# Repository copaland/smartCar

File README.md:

# smartCar
Arduino Bluetooth controlled 2WD smart Car

1. Ultrasonic sensor
2. Bluetooth controlled with Button App
3. Bluetooth controlled with Joystic App  

[AF Motor Shield Library] https://github.com/adafruit/Adafruit-Motor-Shield-library

https://arduino.esp8266.com/stable/package_esp8266com_index.json

https://github.com/stm32duino/BoardManagerFiles/raw/master/package_stmicroelectronics_index.json,https://mcudude.github.io/MiniCore/package_MCUdude_MiniCore_index.json,https://arduino.esp8266.com/stable/package_esp8266com_index.json

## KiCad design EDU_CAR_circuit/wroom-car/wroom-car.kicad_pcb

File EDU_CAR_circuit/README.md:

## ESP-WROOM-02 BASE Smat Car Kit

### 1.KiCad 설치 : 회로도 작성, PCB 설계
### 2.Arduino 설치 : Firmware 프로그래밍
### 3.MIT APP Inventor

### ESP-WROOM-02 PIN MAP
1-A0     SENS  
2-D1   5 TRIG  
3-D2   4 ECHO  
4-D3   0 LEFT SENS(FLASH)   
5-D4   2 RIGHT SENS(SDA)  
6-D5  14 AIN(SCL)  
7-D6  12 APWM   
8-D7  13 BPWM   
9-D8  15 BIN    
10-D9  3 RX  BT  
11-D10 1 TX  BT
13-D0 16 LED (Default)  

### Use KiCad virsion 5.1.10

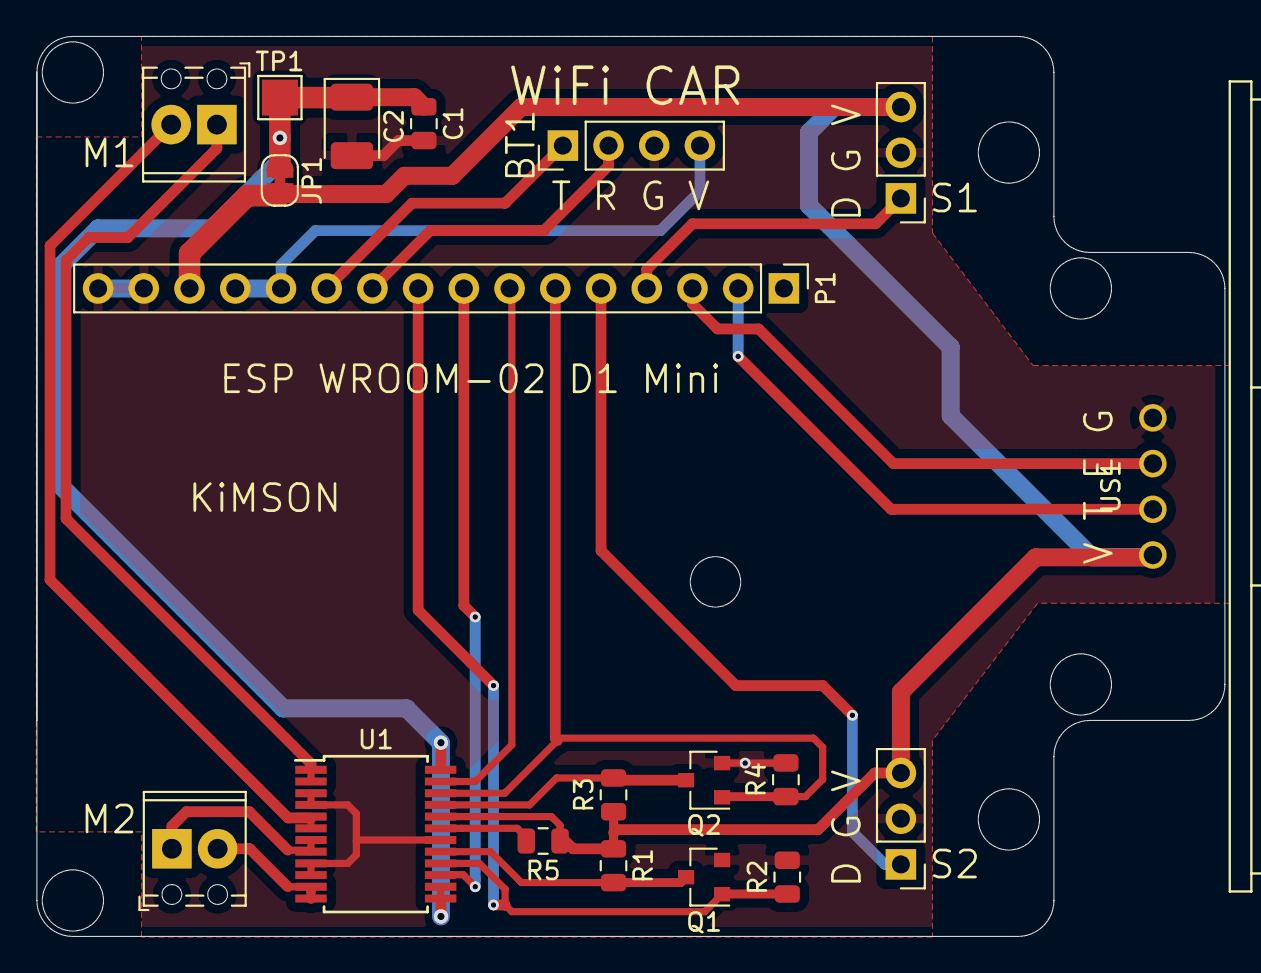
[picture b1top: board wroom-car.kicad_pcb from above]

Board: 2 copper layers, 66.0 x 50.0 mm, 19 parts (0 on the bottom side), 21 nets.

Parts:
BT1: HC-06; PinHeader_1x04_P2.54mm_Vertical
C1: 100nF; C_0805_2012Metric
C2: 22uF; CP_EIA-3528-12_Kemet-T_Pad1.50x2.35mm_HandSolder
JP1: JP; SolderJumper-2_P1.3mm_Bridged_RoundedPad1.0x1.5mm
M1, M2: Screw_Terminal_01x02; TerminalBlock_Phoenix_MPT-0,5-2-2.54_1x02_P2.54mm_Horizontal
P1: Conn_01x16_Male; PinHeader_1x16_P2.54mm_Vertical
Q1, Q2: 2N7002; SOT-23
R1, R2, R3, R4, R5: 10K; R_0805_2012Metric
S1, S2: Conn_01x03_Male; PinHeader_1x03_P2.54mm_Vertical
TP1: TestPoint; TestPoint_Pad_2.0x2.0mm
U1: TB6612FNG; SSOP-24_5.3x8.2mm_P0.65mm
US1: HC-SR04

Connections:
3V3: BT1.4, P1.12, P1.13
+5V: JP1.2, P1.14, R1.1, R3.1, R5.1, S1.3, S2.3, U1.20, US1.1
AIN: P1.6, Q2.1, R4.1, U1.22
APWM: P1.7, U1.23
BIN: P1.9, Q1.1, R2.1, U1.16
BPWM: P1.8, U1.15
ECHO: P1.3, US1.3
GND: BT1.3, C1.2, C2.2, P1.15, P1.16, Q1.2, Q2.2, R2.2, R4.2, S1.2, S2.2, U1.3, U1.4, U1.9, U1.10, U1.18, US1.4
LEFT: P1.4, S1.1
unnamed: M1.1, U1.1, U1.2
unnamed: M1.2, U1.5, U1.6
unnamed: M2.1, U1.7, U1.8
unnamed: M2.2, U1.11, U1.12
unnamed: Q1.3, R1.2, U1.17
unnamed: Q2.3, R3.2, U1.21
unnamed: R5.2, U1.19
RIGHT: P1.5, S2.1
RXD: BT1.2, P1.10
TRIG: P1.2, US1.2
TXD: BT1.1, P1.11
VS: C1.1, C2.1, JP1.1, TP1.1, U1.13, U1.14, U1.24

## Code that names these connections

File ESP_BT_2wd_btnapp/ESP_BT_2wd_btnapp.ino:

/*  20211030 ok
 *  2WD 블루투스 버튼 제어 주행 프로그램 
 *  ESP-WROOM-02 D1
D0  16 LED PULLUP 10K
D1  5 TRIG
D2  4 ECHO
D3  0      FLASH
D4  2      (SDA)
D5  14 AIN (SCL)
D6  12 APWM
D7  13 BPWM
D8  15 BIN PULLDOWN 10K 
D9  TX 1 RXD BT
D10 RX 3 TXD BT
*/
#include <ESP8266WiFi.h>
#include <WiFiCar_TB6612.h> //TB6612
#include <SoftwareSerial.h>

// pin settings
#define LED_PIN    16  //D0 
#define TRIG_PIN    5   //D1 ULTRASONIC
#define ECHO_PIN    4   //D2 

//#define OC1_PIN    0   //D3 NOT USE
//#define OC2_PIN    2   //D4 NOT USE

#define AIN_PIN    14   //D5 TB6612
#define APWM_PIN   12   //D6 
#define BPWM_PIN   13   //D7 
#define BIN_PIN    15   //D8 

#define RXD_PIN   3   //D9 BLUETOOTH TX 
#define TXD_PIN   1   //D10 BLUETOOTH RX

const int ADIR = 1; //Value can be 1 or -1
const int BDIR = 1;

SoftwareSerial BT(RXD_PIN,TXD_PIN);//3RX, 1TX

Motor M1(AIN_PIN, APWM_PIN, ADIR);//Left
Motor M2(BIN_PIN, BPWM_PIN, BDIR);//Right

char command;
int SPEED = 0;//motor speed 1023

bool LEDstatus = LOW;
boolean FL = false;
boolean FR = false;

void setup() { 
  pinMode(LED_PIN, OUTPUT);
  pinMode(TRIG_PIN, OUTPUT);
  pinMode(AIN_PIN, OUTPUT);
  pinMode(BIN_PIN, OUTPUT);
  pinMode(APWM_PIN, OUTPUT);
  pinMode(BPWM_PIN, OUTPUT);
  digitalWrite(AIN_PIN, LOW);
  digitalWrite(BIN_PIN, LOW);
  digitalWrite(APWM_PIN, LOW);
  digitalWrite(BPWM_PIN, LOW);  
//for Test
/*  
  M1.drive(1020,1000);
  M1.brake();
  M2.drive(1020,1000);
  M2.brake();
*/
  brake(M1, M2); //initialize with motors stoped
  
  Serial.begin(9600); //Set the baud rate to your Bluetooth module.
  BT.begin(9600);   
} 

void loop(){ 

  while (BT.available() > 0) {
    command = BT.read();
    ///Serial.print(command);
  }

  if (FL) {digitalWrite(LED_PIN, HIGH);}
  if (!FL) {digitalWrite(LED_PIN, LOW);}

  switch (command) {
    case 'F':SPEED = 980; forward(M1, M2, SPEED); break;
    case 'B':SPEED = 980; backward(M1, M2, -SPEED); break;
    case 'L':SPEED = 900; left(M1, M2, SPEED); break;
    case 'R':SPEED = 900; right(M1, M2, SPEED); break;
    case 'U':SPEED = 900; selfLeft(M1, M2, SPEED); break;
    case 'V':SPEED = 900; selfRight(M1, M2, SPEED); break;
    case 'X':FL = true; break;
    case 'x':FL = false; break;
    case 's':
    default :SPEED = 0; brake(M1, M2); break;

  }
  delay(10);
}

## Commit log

2021-08-09 2WD bluetooth controlled smart car
    # 2WD bluetooth controlled smart car
    1.Ultrasonic Sensor
    2.Bluetooth Control & Button App
    3.Bluetooth Control & Joystic App
2021-08-09 2WD Smart Car mBlock program with MIT app
    Bluetooth controlled 2WD Smart Car mBlock program with MIT app
2021-09-13 ESP WROOM SMART CAR CIRCUIT
    KiCad circuits and PCBs are uploaded as unfinished files for learning.
2021-09-13 ADD PINMAP & CIRCUIT
    ADD PINMAP & CIRCUIT
2021-09-13 change IMAGE LOCATION
    change IMAGE LOCATION
2021-09-29 Button Image
    Button image to create app
2021-09-29 Upload Button image
    Button image to create app
2021-09-29 Bluetooth button control Apk
    Bluetooth button control Apk file for SmartCar
2021-10-27 Upload files New
    빠진 부품 수정함
2021-10-28 TB6612 MOTOR DRIVE LIBRARY FILES
    Upload TB6612 MOTOR DRIVE LIBRARY FILES
2021-10-28 Add files WiFi esp-wroom-02
    Add files WiFi esp-wroom-02
2021-10-30 2WD ESP Wroom 02 Bluetooth Control
    2WD ESP Wroom 02 Bluetooth Control Program
2021-10-30 Create README.md
    설명서 추가
2021-10-30 ESP wroom 02 - Bluetooth App
    ESP wroom 02 - Bluetooth App for MIT App Inventor
2021-11-13 Add files App image
    Image files used by the app
2021-11-13 WiFi Car ESP8266 App PPT
    WiFi Car ESP8266 App PPT
2021-11-22 2WD Car Project for ESP-Wroom
    Bluetooth Controlled 2WD Car Project for ESP-Wroom Board
2021-12-16 WIFI CAR ontrol AP Mode
    WIFI CAR ontrol AP Mode with APP
2021-12-16 2WD BT CAR no Use lib
